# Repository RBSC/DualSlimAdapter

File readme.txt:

--------------------------------------------------------------------------------
DualSlim Adapter Board v1.1
Copyright (c) 2022 RBSC
--------------------------------------------------------------------------------

About
-----

This is the adapter board to connect two slim floppy drives to a single 34-pin FDD interface cable. There could be also a combination
of a slim floppy drive, for example MPF820 and a slim Gotek drive, for example SFRM72-DU26. Now you don't need to have 2 drive bays
in your MSX computer - you can have 2 drives in a single bay!

The 3D printed parts to join 2 slim drives into one solution, suitable for a single drive bay can be found here:
https://www.thingiverse.com/thing:5445185

See the pictures in the Pics folder on how to assemble and install the DualSlim setup in MSX2 computer that has a single floppy drive
bay. Note the picture for the AX-350 MSX2 fix - you will need to solder one wire for the DualSlim setup in this computer.

The video of DualSlim setup in the Yamaha AX-350 computer can be seen here:
https://www.youtube.com/watch?v=o-ZJfZNqkJk

Parts
-----

Beside the circuit board, you will need the following parts:

 - 4-pin male floppy drive power connector (angled pins)
 - 34-pin (or longer) dual-row angled pin header with 2.54mm spacing
 - Two 26-pin FPC ribbon flexible flat cable, 1mm spacing, 100mm long, reverse type!
 - Two 26-pin FPC/FFC connectors with 1.0mm spacing

These parts are available here (at the time of writing):

https://www.aliexpress.com/item/1005001582299405.html
https://www.aliexpress.com/item/4000373321138.html
https://www.aliexpress.com/item/1005001789411803.html
https://www.aliexpress.com/item/33043163402.html

The slim Gotek drive can be bought from here:

https://www.aliexpress.com/item/1005004265960945.html

All parts are mounted on the top of the board. When installing the board into a computer, make sure to isolate the back side of
the circuit board.

IMPORTANT!
----------

The RBSC provides all the files and information for free, without any liability (see the disclaimer.txt file). The provided information,
software or hardware must not be used for commercial purposes unless permitted by the RBSC. Producing a small amount of bare boards for
personal projects and selling the rest of the batch is allowed without the permission of RBSC.

When the sources of the tools are used to create alternative projects, please always mention the original source and the copyright!

Contact information
-------------------

The members of RBSC group Tnt23, Wierzbowsky, Pyhesty, Ptero, GreyWolf, SuperMax and DJS3000 can be contacted via the group's e-mail
address:

info@rbsc.su

The group's coordinator could be reached via this e-mail address:

admin@rbsc.su

The group's website can be found here:

https://rbsc.su/
https://rbsc.su/ru

The RBSC's hardware repository can be found here:

https://github.com/rbsc

The RBSC's 3D model repository can be found here:

https://www.thingiverse.com/groups/rbsc/things

-= ! MSX FOREVER ! =-

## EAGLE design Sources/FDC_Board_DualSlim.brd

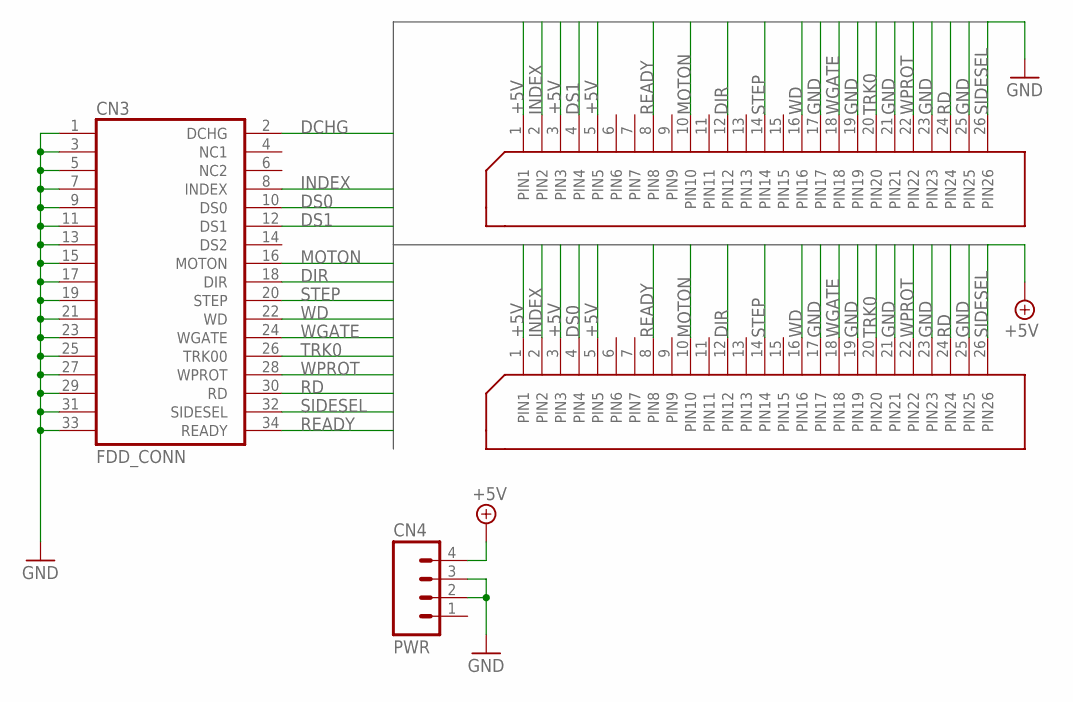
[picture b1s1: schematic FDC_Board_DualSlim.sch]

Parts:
CN1, CN2: FDC_26; FDC26
CN3: FDD_CONN
CN4: PWR; 1X04_LONGPADS

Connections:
+5V: CN1.1 (PIN1), CN1.3 (PIN3), CN1.5 (PIN5), CN2.1 (PIN1), CN2.3 (PIN3), CN2.5 (PIN5), CN4.4
DCHG: CN3.2 (DCHG)
DIR: CN1.12 (PIN12), CN2.12 (PIN12), CN3.18 (DIR)
DS0: CN1.4 (PIN4), CN3.10 (DS0)
DS1: CN2.4 (PIN4), CN3.12 (DS1)
GND: CN1.17 (PIN17), CN1.19 (PIN19), CN1.21 (PIN21), CN1.23 (PIN23), CN1.25 (PIN25), CN2.17 (PIN17), CN2.19 (PIN19), CN2.21 (PIN21), CN2.23 (PIN23), CN2.25 (PIN25), CN3.1, CN3.3, CN3.5, CN3.7, CN3.9, CN3.11, CN3.13, CN3.15, CN3.17, CN3.19, CN3.21, CN3.23, CN3.25, CN3.27, CN3.29, CN3.31, CN3.33, CN4.2, CN4.3
INDEX: CN1.2 (PIN2), CN2.2 (PIN2), CN3.8 (INDEX)
MOTON: CN1.10 (PIN10), CN2.10 (PIN10), CN3.16 (MOTON)
RD: CN1.24 (PIN24), CN2.24 (PIN24), CN3.30 (RD)
READY: CN1.8 (PIN8), CN2.8 (PIN8), CN3.34 (READY)
SIDESEL: CN1.26 (PIN26), CN2.26 (PIN26), CN3.32 (SIDESEL)
STEP: CN1.14 (PIN14), CN2.14 (PIN14), CN3.20 (STEP)
TRK0: CN1.20 (PIN20), CN2.20 (PIN20), CN3.26 (TRK00)
WD: CN1.16 (PIN16), CN2.16 (PIN16), CN3.22 (WD)
WGATE: CN1.18 (PIN18), CN2.18 (PIN18), CN3.24 (WGATE)
WPROT: CN1.22 (PIN22), CN2.22 (PIN22), CN3.28 (WPROT)

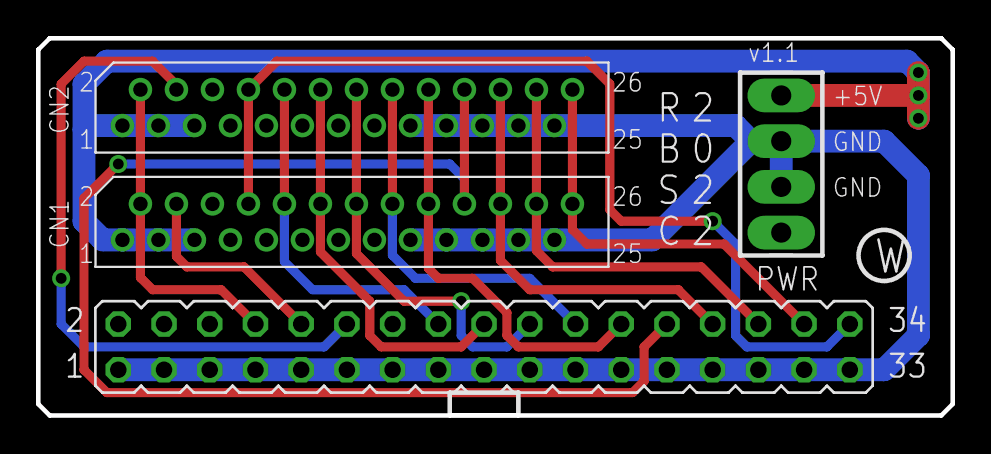
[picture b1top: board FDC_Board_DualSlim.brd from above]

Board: 2 copper layers, 50.8 x 21.0 mm, 4 parts (0 on the bottom side), 15 nets.

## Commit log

2022-07-30 :octocat: Added .gitattributes & .gitignore files
2022-07-30 Initial release 31.07.2022
    Initial release of the DualSlim adapter
2022-07-31 Initial release 31.07.2022
    Updated readme
2022-07-31 Updated 31.07.2022
    Updated readme

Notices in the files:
parts and their libraries:
SparkFun-Connectors: Licensing: Creative Commons ShareAlike 4.0 International - https://creativecommons.org/licenses/by-sa/4.0
